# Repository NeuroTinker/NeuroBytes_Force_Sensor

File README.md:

# NeuroBytes Pressure Sensory Neuron

The NeuroBytes Pressure Sensory Neuron is an open-source hardware neuron simulator designed and sold by [NeuroTinker, LLC](http://www.neurotinker.com/). 

All NeuroBytes products are based on the ST32L0x series of ARM Cortex-M0+ 32-bit microcontrollers. The boards were designed in KiCad and Inkscape and are released under the terms of the Creative Commons Attribution-ShareAlike 4.0 license, available here: http://creativecommons.org/licenses/by-sa/4.0/. The NeuroBytes Pressure Sensory Neuron is Certified Open Source Hardware as defined by [OSHWA](https://www.oshwa.org), certification number US000111.

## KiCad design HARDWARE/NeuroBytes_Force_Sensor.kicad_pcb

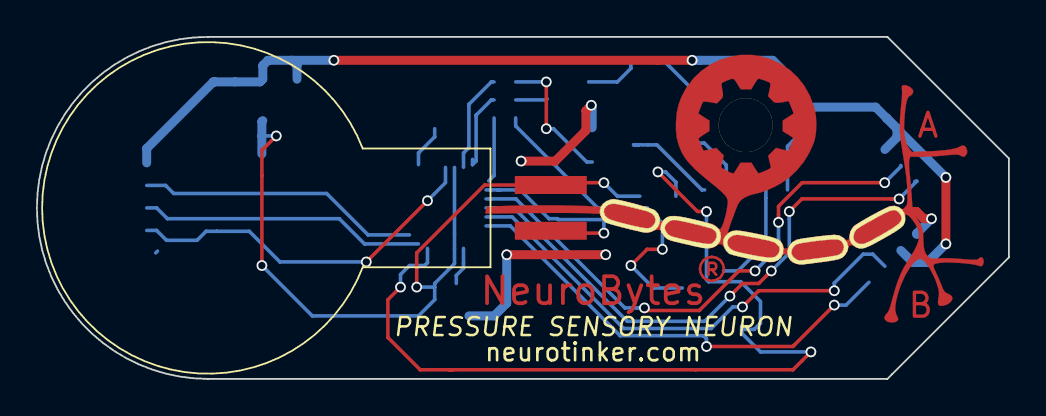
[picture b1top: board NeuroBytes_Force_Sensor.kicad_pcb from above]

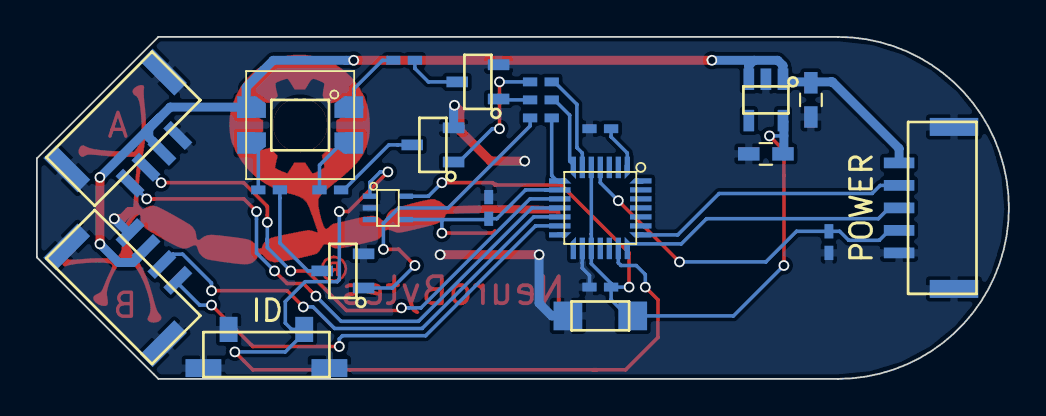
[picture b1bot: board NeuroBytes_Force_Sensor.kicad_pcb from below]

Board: 2 copper layers, 54.0 x 19.0 mm, 25 parts (24 on the bottom side), 25 nets.

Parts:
C1, C4: 1u; C_0603_HandSoldering
C2: 10u; ZF_SMD_nonpol_1206
C3, C5: 0u1; ZF_SMD_NonPol_0402_cap
D1: LED_RABG; ZF_LED_RGB_SunLED_XZMDKCBDDG45S-9_cast
P1: JST_GH_5-pos; ZF_CONN_JST_GH_5POS
P6, P7: CONN_01X04; ZF_CONN_JST_GH
Q1, Q2, Q3: MMBT3904; ZF_SOT23-3L
R1: 150; ZF_SMD_NonPol_0402
R2, R3: 100; ZF_SMD_NonPol_0402
R4: JMP; ZF_SMD_NonPol_0402
R5, R6, R7: 1k; ZF_SMD_NonPol_0402
R8: 10k; ZF_SMD_NonPol_0402
R9: R_Variable; ZF_SENSOR_FSR_34-00015
SW1: SW_PUSH; ZF_SW_Momentary_SideMtg
U1: STM32L011Gx; ZF_IC_UFQFPN28-050
U2: 3v3 LDO; ZF_SOT23-5L
U3: RClamp0503F; ZF_SMD_SOT-353

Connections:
+3V3: C2.1, C3.1, C4.1, R9.2, U1.5, U1.17, U2.5, U3.5
+5V: C1.1, D1.2, P1.5, P6.2, P7.2, U2.1, U2.3
A1EX: P6.4, U1.11
A1IN: P6.3, U1.10
A2EX: P7.4, U1.13
A2IN: P7.3, U1.12
GND: C1.2, C2.2, C3.2, C4.2, C5.2, P1.1, P6.1, P7.1, Q1.2, Q2.2, Q3.2, R4.1, R8.2, SW1.1, U1.16, U2.2, U3.2
IDENTIFY: SW1.2, U1.20, U3.1
LED_B: R7.2, U1.8
LED_G: R6.2, U1.6
LED_R: R5.2, U1.7
unnamed: D1.1, R1.1
unnamed: D1.3, R3.1
unnamed: D1.4, R2.1
unnamed: Q1.1, R5.1
unnamed: Q1.3, R1.2
unnamed: Q2.1, R6.1
unnamed: Q2.3, R2.2
unnamed: Q3.1, R7.1
unnamed: Q3.3, R3.2
unnamed: R4.2, U1.1
RESET: C5.1, P1.2, U1.4
SENSE: R8.1, R9.1, U1.9, U3.4
SWCLK: P1.4, U1.22
SWDIO: P1.3, U1.21

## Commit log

2017-04-24 Initial commit -- first rev hardware and test firmware.
2017-05-15 added schematic library submodule
2017-05-17 Second PCB spin. Added unipolar neuron graphics and changed indication mode to 'traditional' NeuroTinker bottom-mount RGB LED. Added letters for dendrites. Updated title block to standard format. Man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
2017-05-25 removed libopencm3 submodules that link back to the libopencm3 project (need to relink to NeuroTinker fork)
2017-05-25 Updated libopencm3 submodule to reference NeuroTinker fork
2017-05-25 Got rid of compiled files. Updated schematic LED global labels to correct values. Updated HAL.c and HAL.h to new hardware design (neuron graphics, RGB LED, etc). Changed main.c to simple test program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
2017-06-29 fix bug
2017-06-29 Updated PCB design files. Generated paste Gerber for stencil.
2017-06-29 added neuron functionality
2017-07-04 sped up
2017-08-11 reorganized
2017-08-11 cleaned up
2017-08-11 updated structure
2017-08-11 added fingerprint
2017-08-11 updated power connector to 5-pin JST GH. minor routing/labeling changes.
2017-08-11 changed fingerprint
2017-08-28 added kicad text to *.svg file. added *.png render of board front.
2017-09-05 updated illustrations
2017-09-06 illustration updates
2017-09-06 fresh *.png exports
2017-09-06 added board back img
2017-09-11 fixed simultaneous axon-dendrite excitation issue
2017-09-11 made elf
2017-09-20 removed old design files from dev branch
2017-09-20 update dev branch with hardware files from master
2017-09-20 changed to Pressure Sensory Neuron
2017-09-20 updated *.png exports to reflect new name
2017-09-22 cleaned up /FIRMWARE and resolved merge conflicts
2017-09-22 removed merge decorations
2017-09-22 updated to new gear on *.svg and PCB. pulled back mask on labels. other minor updates.
2017-09-22 removed dual transistors and resistor network. started updating component details.
2017-09-23 added single NPN transitors and non-networked resistors for LED. fresh fab file exports. added fab notes. other minor updates.
2017-10-03 page layout updates
2017-11-29 reduce LED brightness
2017-11-29 updated license to CC-BY-SA 4.0 and readme. added drawing number to PCB.
2018-01-30 works with common. prep for merge
2018-01-30 fixed adaptation
2018-02-12 added ESD protection
2018-03-08 updated PCB render text
2018-03-08 more minor PCB render updates. really just chasing green squares at this point
2018-03-08 added OSHWA cert logo to README.md
2018-04-10 made elf. (arizona build)
2018-05-23 generated fab files. added BOM.
2018-05-23 updated INSERT attribute. regenerated footprint position file.
2018-05-31 exported schematic *.pdf. updated LDO symbol.
2018-08-08 updated footprints to include B.Fab outlines. minor routing changes. re-generated Gerbers. added placement pdf.
2018-08-08 regen drill file
2018-12-28 changed device id to 6
2018-12-29 increased AP brightness

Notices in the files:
HARDWARE/NeuroBytes_Force_Sensor.kicad_pcb:
(C) 2017 Zach Fredin
License: CC-BY-SA 4.0
